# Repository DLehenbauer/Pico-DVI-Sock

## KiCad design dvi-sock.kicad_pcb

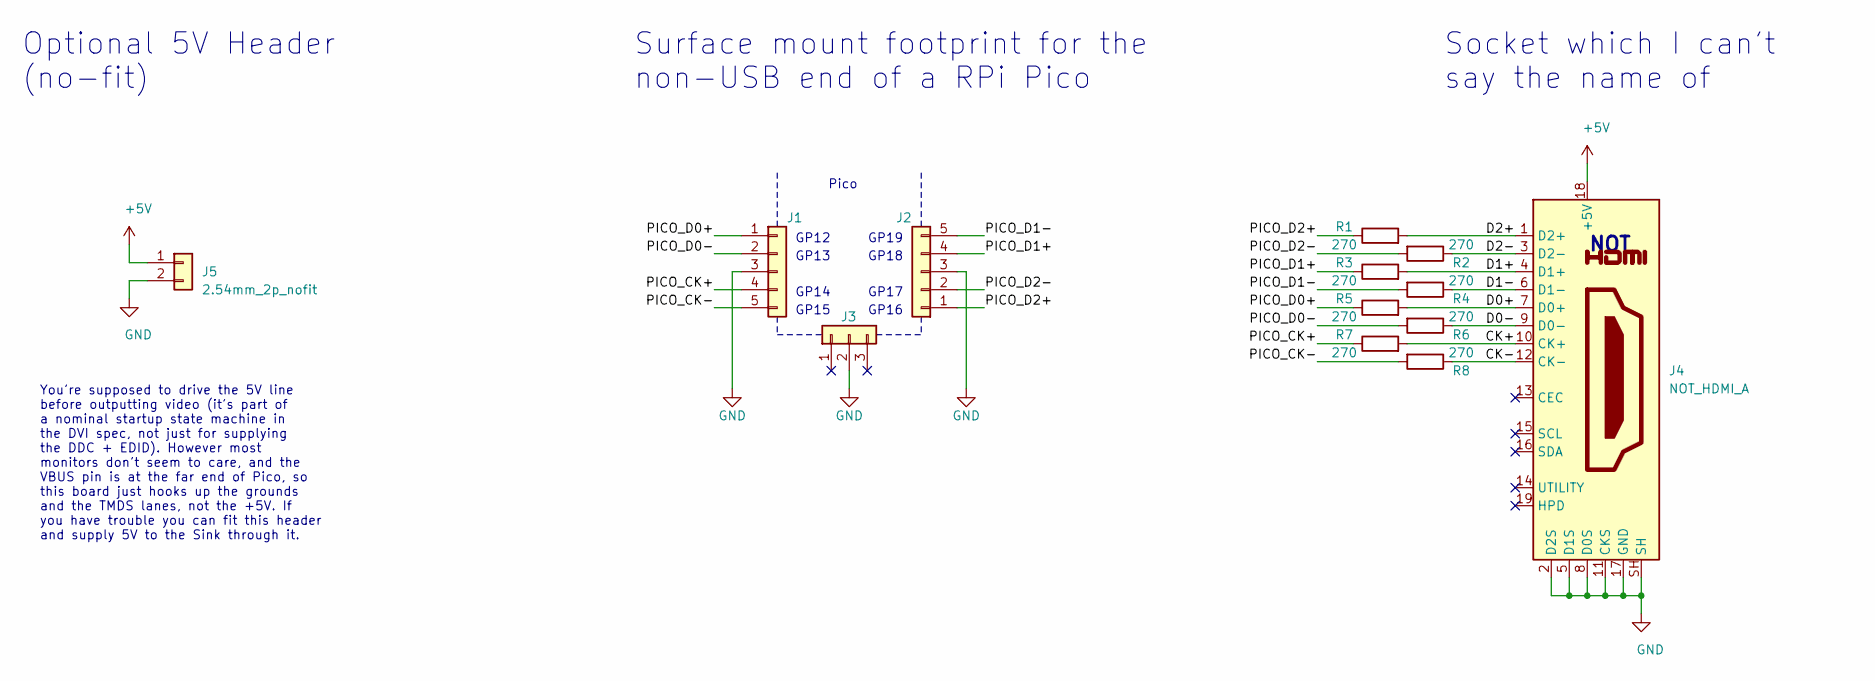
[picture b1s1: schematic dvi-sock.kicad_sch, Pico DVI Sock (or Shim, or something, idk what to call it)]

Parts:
J1, J2: Conn_01x05; castellated_2.54mm_smd_x5
J3: Conn_01x03; castellated_2.54mm_smd_x3
J4: NOT_HDMI_A; HDMI_A_Molex_208658-1001_Horizontal; LCSC C138388
J5: 2.54mm_2p_nofit; PinHeader_1x02_P2.54mm_Vertical_nosilk
R1, R2, R3, R4, R5, R6, R7, R8: 270; R_0603_1608Metric; LCSC C22966

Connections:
+5V: J4.18 (+5V), J5.1
/CK+: J4.10 (CK+), R7.2
/CK-: J4.12 (CK-), R8.1
/D0+: J4.7 (D0+), R5.2
/D0-: J4.9 (D0-), R6.1
/D1+: J4.4 (D1+), R3.2
/D1-: J4.6 (D1-), R4.1
/D2+: J4.1 (D2+), R1.2
/D2-: J4.3 (D2-), R2.1
/PICO_CK+: J1.4, R7.1
/PICO_CK-: J1.5, R8.2
/PICO_D0+: J1.1, R5.1
/PICO_D0-: J1.2, R6.2
/PICO_D1+: J2.4, R3.1
/PICO_D1-: J2.5, R4.2
/PICO_D2+: J2.1, R1.1
/PICO_D2-: J2.2, R2.2
GND: J1.3, J2.3, J3.2, J4.2 (D2S), J4.5 (D1S), J4.8 (D0S), J4.11 (CKS), J4.17 (GND), J4.SH, J5.2

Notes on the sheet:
GP12
GP15
GP17
You're supposed to drive the 5V line before outputting video (it's part of a nominal startup state machine in the DVI spec, not just for supplying the DDC + EDID). However most monitors don't seem to care, and the VBUS pin is at the far end of Pico, so this board just hooks up the grounds and the T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
GP13
Surface mount footprint for the non-USB end of a RPi Pico
GP14
GP19
GP18
NOT
Pico
Optional 5V Header (no-fit)
Socket which I can't say the name of
GP16

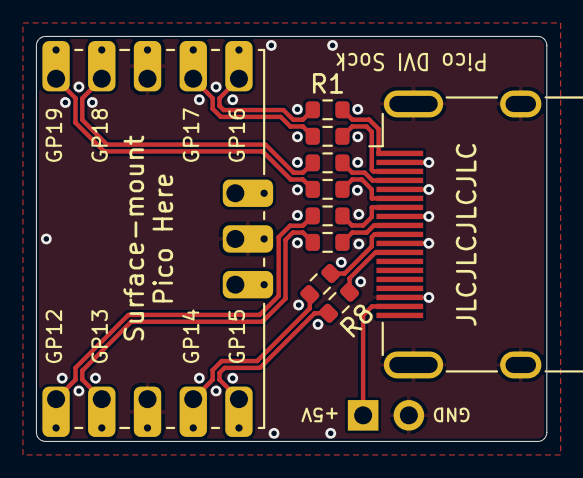
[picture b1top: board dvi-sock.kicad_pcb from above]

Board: 2 copper layers, 28.4 x 22.5 mm, 13 parts (0 on the bottom side), 18 nets.

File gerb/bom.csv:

Designator,Footprint,Quantity,Value,LCSC Part #
"J1, J2",castellated_2.54mm_smd_x5,2,Conn_01x05,
J3,castellated_2.54mm_smd_x3,1,Conn_01x03,
J4,HDMI_A_Molex_208658-1001_Horizontal,1,NOT_HDMI_A,C138388
J5,PinHeader_1x02_P2.54mm_Vertical_nosilk,1,2.54mm_2p_nofit,
"R1, R2, R3, R4, R5, R6, R7, R8",R_0603_1608Metric,8,270,C22966

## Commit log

2022-09-16 Automatic conversion to KiCad 6
2022-09-16 Rev B: Use parts available for JLCPCB SMT assembly
